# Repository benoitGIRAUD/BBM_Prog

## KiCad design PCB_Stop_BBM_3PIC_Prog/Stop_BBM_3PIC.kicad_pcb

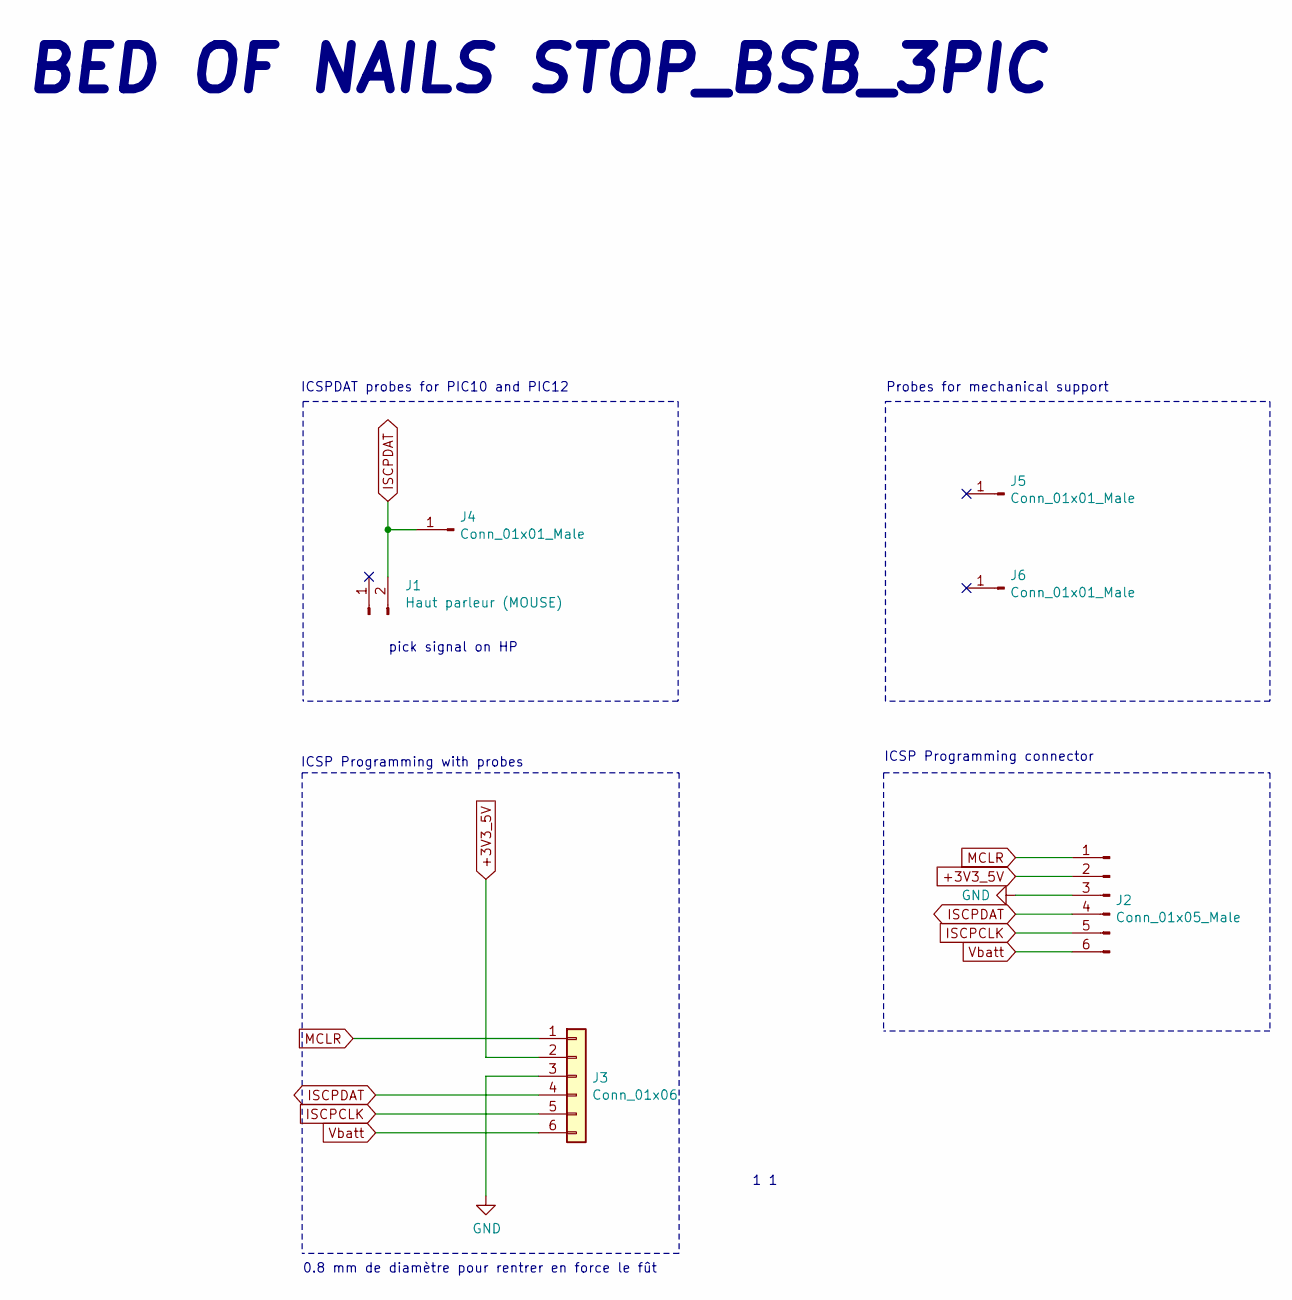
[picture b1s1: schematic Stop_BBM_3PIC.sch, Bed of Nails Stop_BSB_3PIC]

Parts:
J1: Haut parleur (MOUSE); SolderWirePad_1x01_SMD_5x10mm_BBM; Manufacturer PN ABS-209-RC
J2: Conn_01x05_Male; PinHeader_1x06_P2.54mm_Horizontal
J3: Conn_01x06; PinHeader_1x06_P2.54mm_Vertical
J4, J5, J6: Conn_01x01_Male; PinHeader_1x01_P2.54mm_Vertical

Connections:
+3V3_5V: J2.2, J3.2
GND: J2.3, J3.3
ISCPCLK: J2.5, J3.5
ISCPDAT: J1.2, J2.4, J3.4, J4.1
MCLR: J2.1, J3.1
Vbatt: J2.6, J3.6

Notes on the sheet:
1 1
ICSP Programming with probes
BED OF NAILS STOP_BSB_3PIC
ICSP Programming connector
ICSPDAT probes for PIC10 and PIC12
Probes for mechanical support
pick signal on HP
0.8 mm de diamètre pour rentrer en force le fût

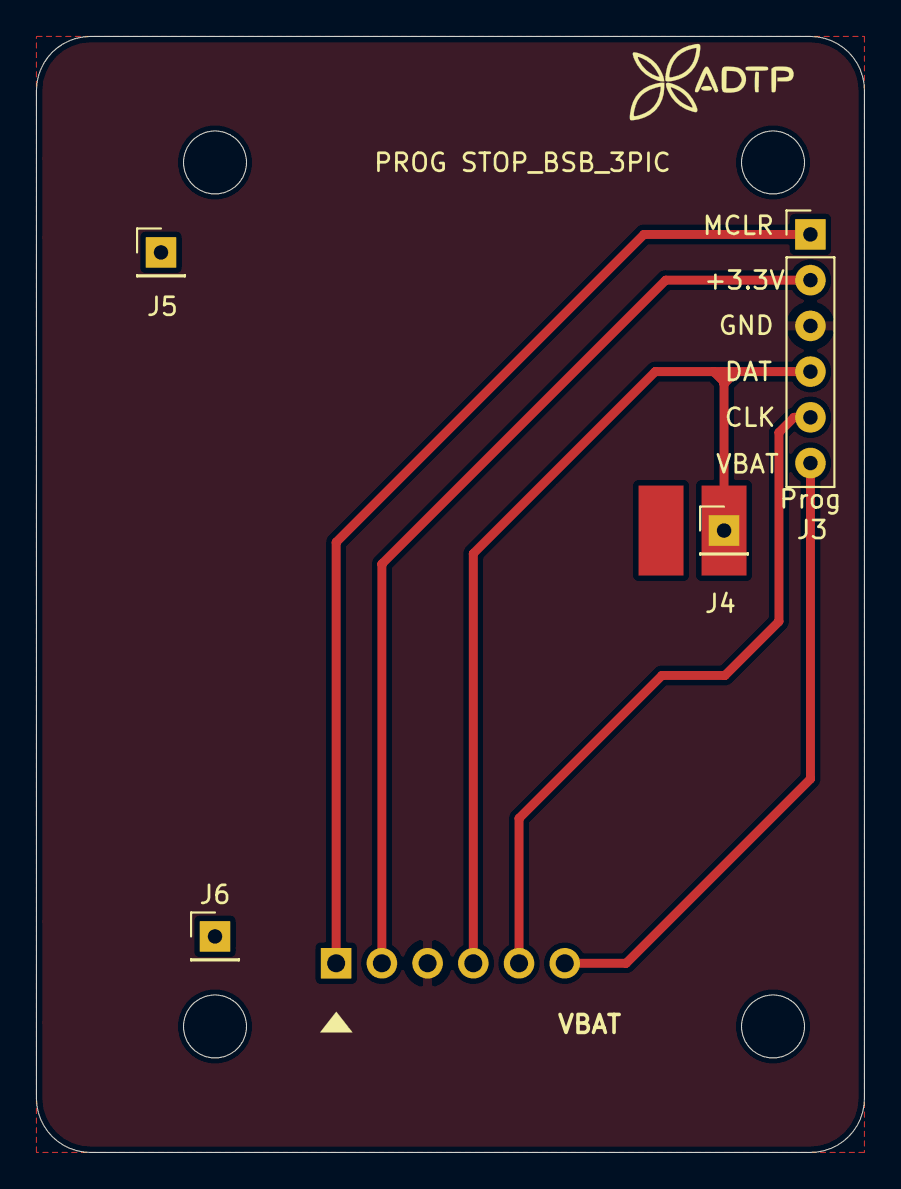
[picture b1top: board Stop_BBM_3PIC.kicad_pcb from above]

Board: 2 copper layers, 46.0 x 62.0 mm, 11 parts (1 on the bottom side), 6 nets.

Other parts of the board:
G21: LOGO; adtp
H1, H2, H3, H4: MountingHole_3.5mm

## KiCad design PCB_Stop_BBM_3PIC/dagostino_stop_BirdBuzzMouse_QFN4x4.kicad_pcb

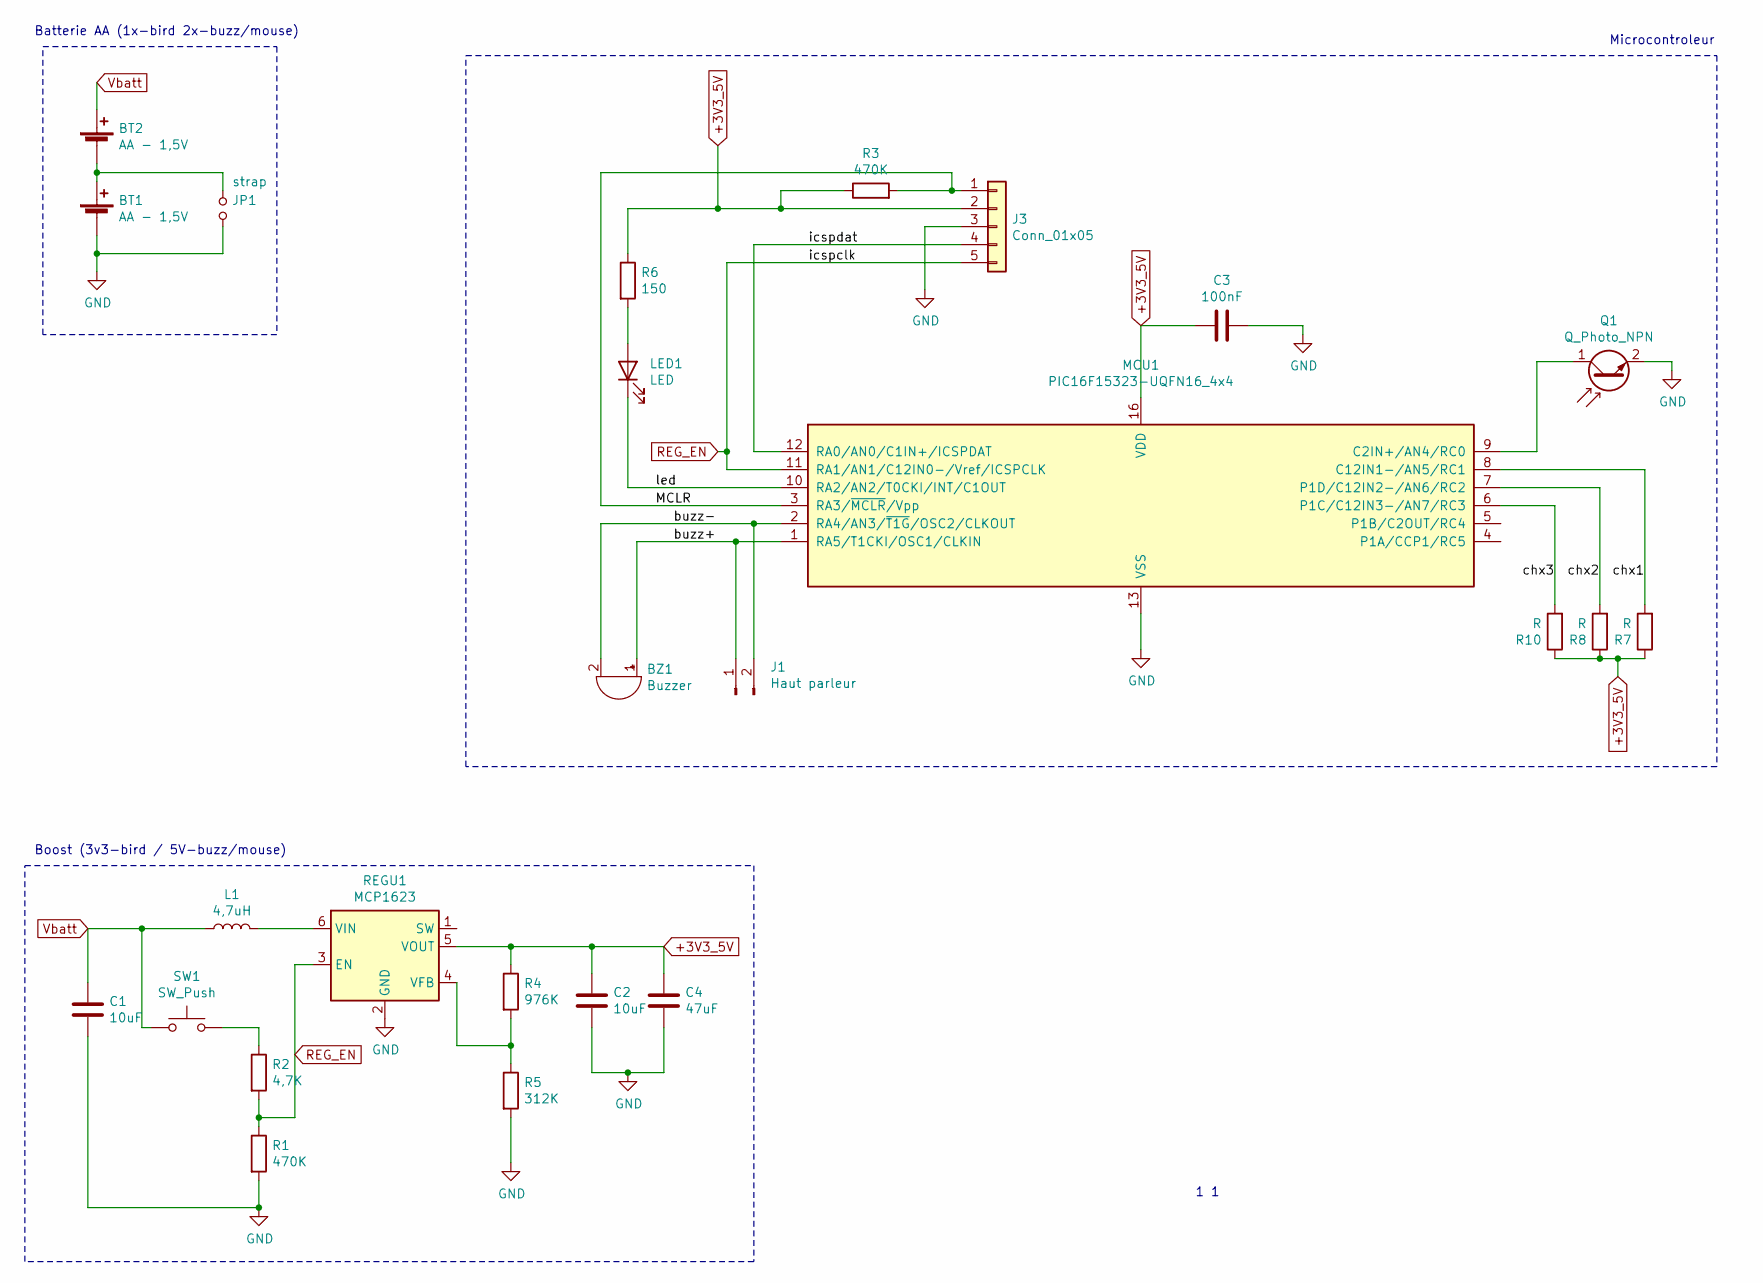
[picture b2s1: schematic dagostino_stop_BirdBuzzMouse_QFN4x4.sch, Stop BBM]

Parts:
BT1, BT2: AA - 1,5V; BatteryHolder_Keystone_2460_1xAA
BZ1: Buzzer; Buzzer_TDK_PS1240P02BT_D12.2mm_H6.5mm
C1: 10uF; C_0805_2012Metric_Pad1.18x1.45mm_HandSolder
C2: 10uF; C_0603_1608Metric_Pad1.08x0.95mm_HandSolder
C3: 100nF; C_0805_2012Metric_Pad1.18x1.45mm_HandSolder
C4: 47uF; C_1206_3216Metric_Pad1.33x1.80mm_HandSolder
J1: Haut parleur; PinHeader_1x02_P2.54mm_Vertical
J3: Conn_01x05; PinHeader_1x05_P2.54mm_Vertical
JP1: strap; SolderJumper-2_P1.3mm_Open_TrianglePad1.0x1.5mm
L1: 4,7uH; C_1210_3225Metric
LED1: LED; LED_0603_1608Metric
MCU1: PIC16F15323-UQFN16_4x4; QFN-16-1EP_4x4mm_P0.65mm_EP2.1x2.1mm; digikey PIC16F15323T-I/JQDKR-ND
Q1: Q_Photo_NPN; LED_1206_3216Metric_Pad1.42x1.75mm_HandSolder
R1, R3: 470K; R_0603_1608Metric_Pad0.98x0.95mm_HandSolder
R2: 4,7K; R_0603_1608Metric_Pad0.98x0.95mm_HandSolder
R4: 976K; R_0603_1608Metric_Pad0.98x0.95mm_HandSolder
R5: 312K; R_0603_1608Metric_Pad0.98x0.95mm_HandSolder
R6: 150; R_0603_1608Metric_Pad0.98x0.95mm_HandSolder
R7, R8, R10: R; SolderJumper-2_P1.3mm_Open_TrianglePad1.0x1.5mm
REGU1: MCP1623; SOT-23-6
SW1: SW_Push; SW_Push_1P1T_NO_6x6mm_H9.5mm

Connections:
+3V3_5V: C2.1, C3.1, C4.1, J3.2, MCU1.16 (VDD), R3.1, R4.1, R6.1, R7.1, R8.1, R10.1, REGU1.5 (VOUT)
/MCLR: J3.1, MCU1.3 (RA3/~MCLR~/Vpp), R3.2
/buzz+: BZ1.1 (-), J1.1, MCU1.1 (RA5/T1CKI/OSC1/CLKIN)
/buzz-: BZ1.2 (+), J1.2, MCU1.2 (RA4/AN3/~T1G~/OSC2/CLKOUT)
/chx1: MCU1.8 (C12IN1-/AN5/RC1), R7.2
/chx2: MCU1.7 (P1D/C12IN2-/AN6/RC2), R8.2
/chx3: MCU1.6 (P1C/C12IN3-/AN7/RC3), R10.2
/icspdat: J3.4, MCU1.12 (RA0/AN0/C1IN+/ICSPDAT)
/led: LED1.1 (K), MCU1.10 (RA2/AN2/T0CKI/INT/C1OUT)
GND: BT1.2 (-), C1.2, C2.2, C3.2, C4.2, J3.3, JP1.2, MCU1.13 (VSS), Q1.2 (E), R1.2, R5.2, REGU1.2 (GND)
unnamed: BT1.1 (+), BT2.2 (-), JP1.1
unnamed: L1.2, REGU1.6 (VIN)
unnamed: LED1.2 (A), R6.2
unnamed: MCU1.9 (C2IN+/AN4/RC0), Q1.1 (C)
unnamed: R2.1, SW1.2
unnamed: R4.2, R5.1, REGU1.4 (VFB)
REG_EN: J3.5, MCU1.11 (RA1/AN1/C12IN0-/Vref/ICSPCLK), R1.1, R2.2, REGU1.3 (EN)
Vbatt: BT2.1 (+), C1.1, L1.1, SW1.1

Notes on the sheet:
Batterie AA (1x-bird 2x-buzz/mouse)
Microcontroleur
Boost (3v3-bird / 5V-buzz/mouse)
1 1

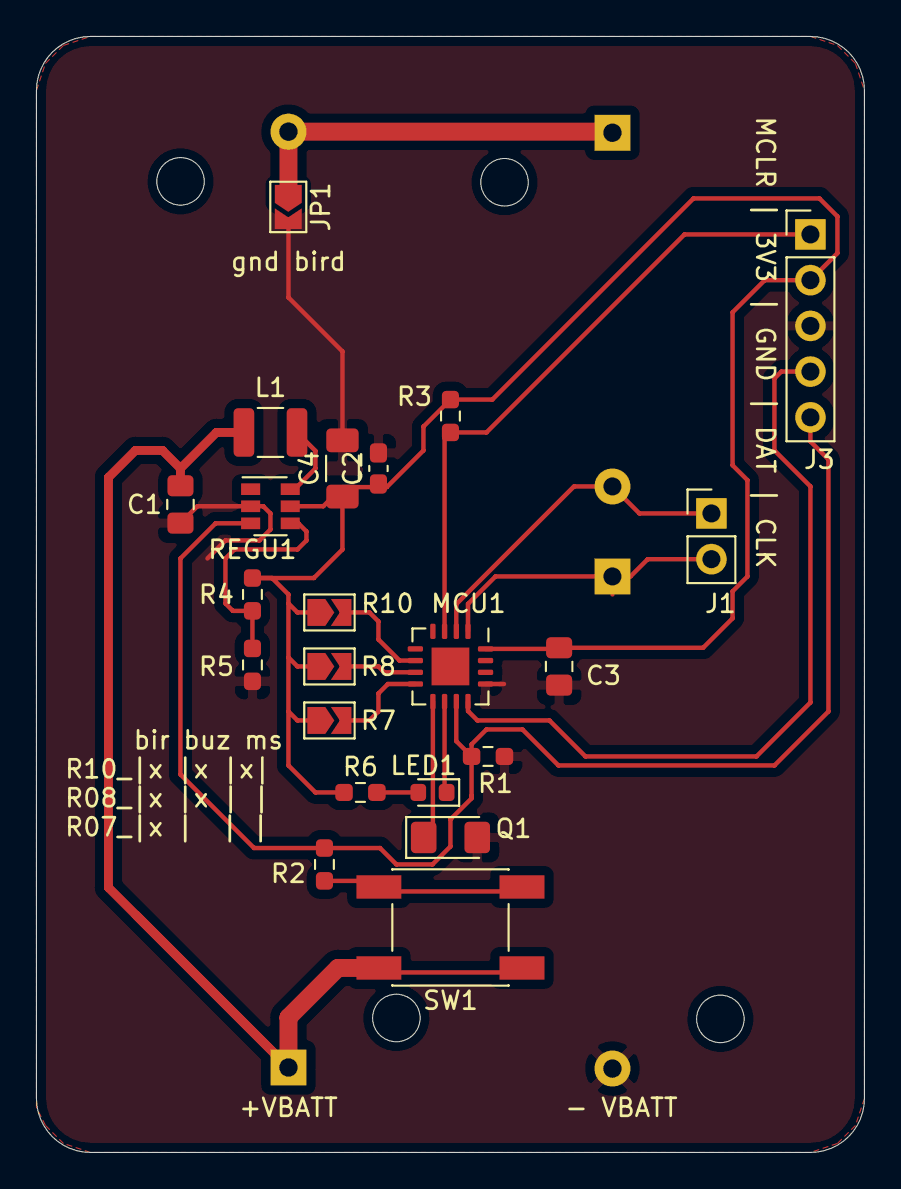
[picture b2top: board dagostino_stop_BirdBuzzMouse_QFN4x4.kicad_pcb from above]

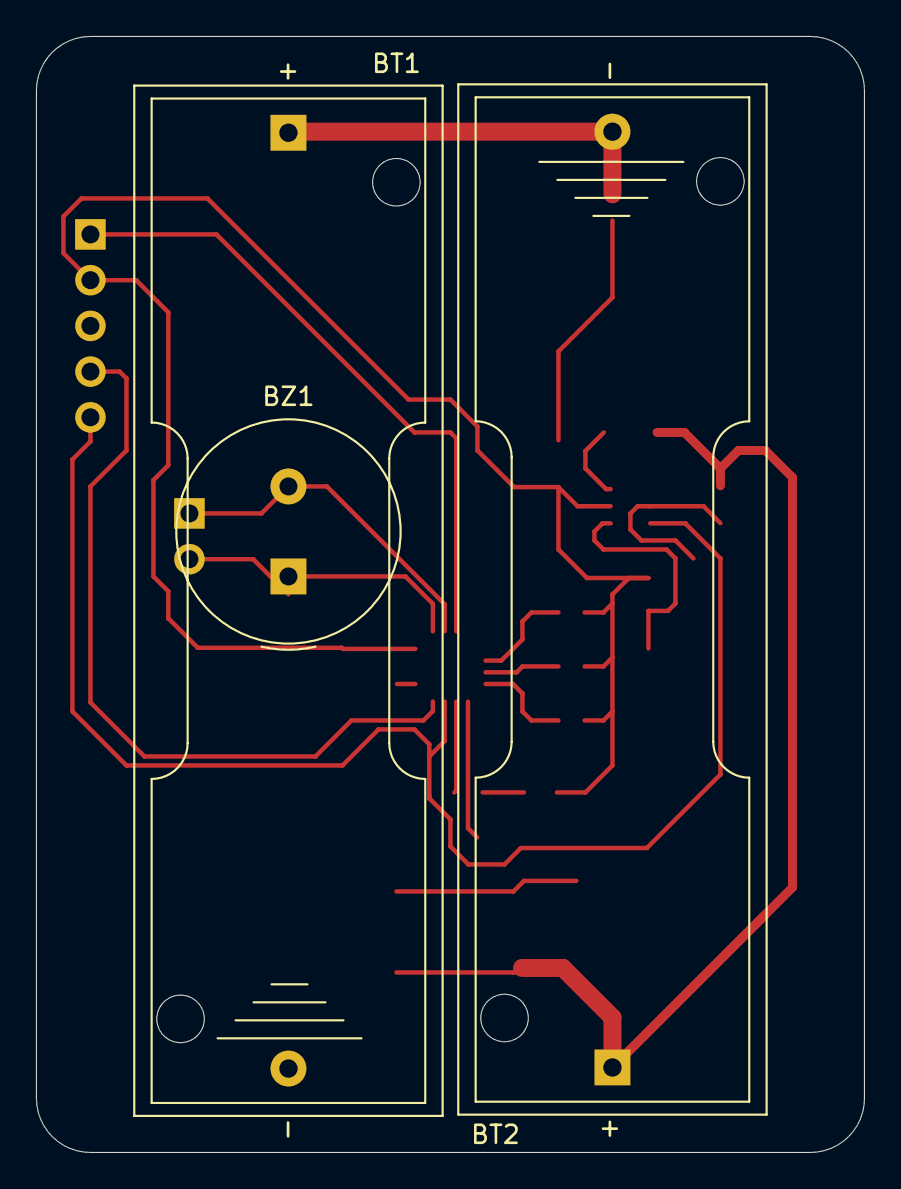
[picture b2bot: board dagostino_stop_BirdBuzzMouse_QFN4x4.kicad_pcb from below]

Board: 2 copper layers, 46.0 x 62.0 mm, 25 parts (3 on the bottom side), 18 nets.

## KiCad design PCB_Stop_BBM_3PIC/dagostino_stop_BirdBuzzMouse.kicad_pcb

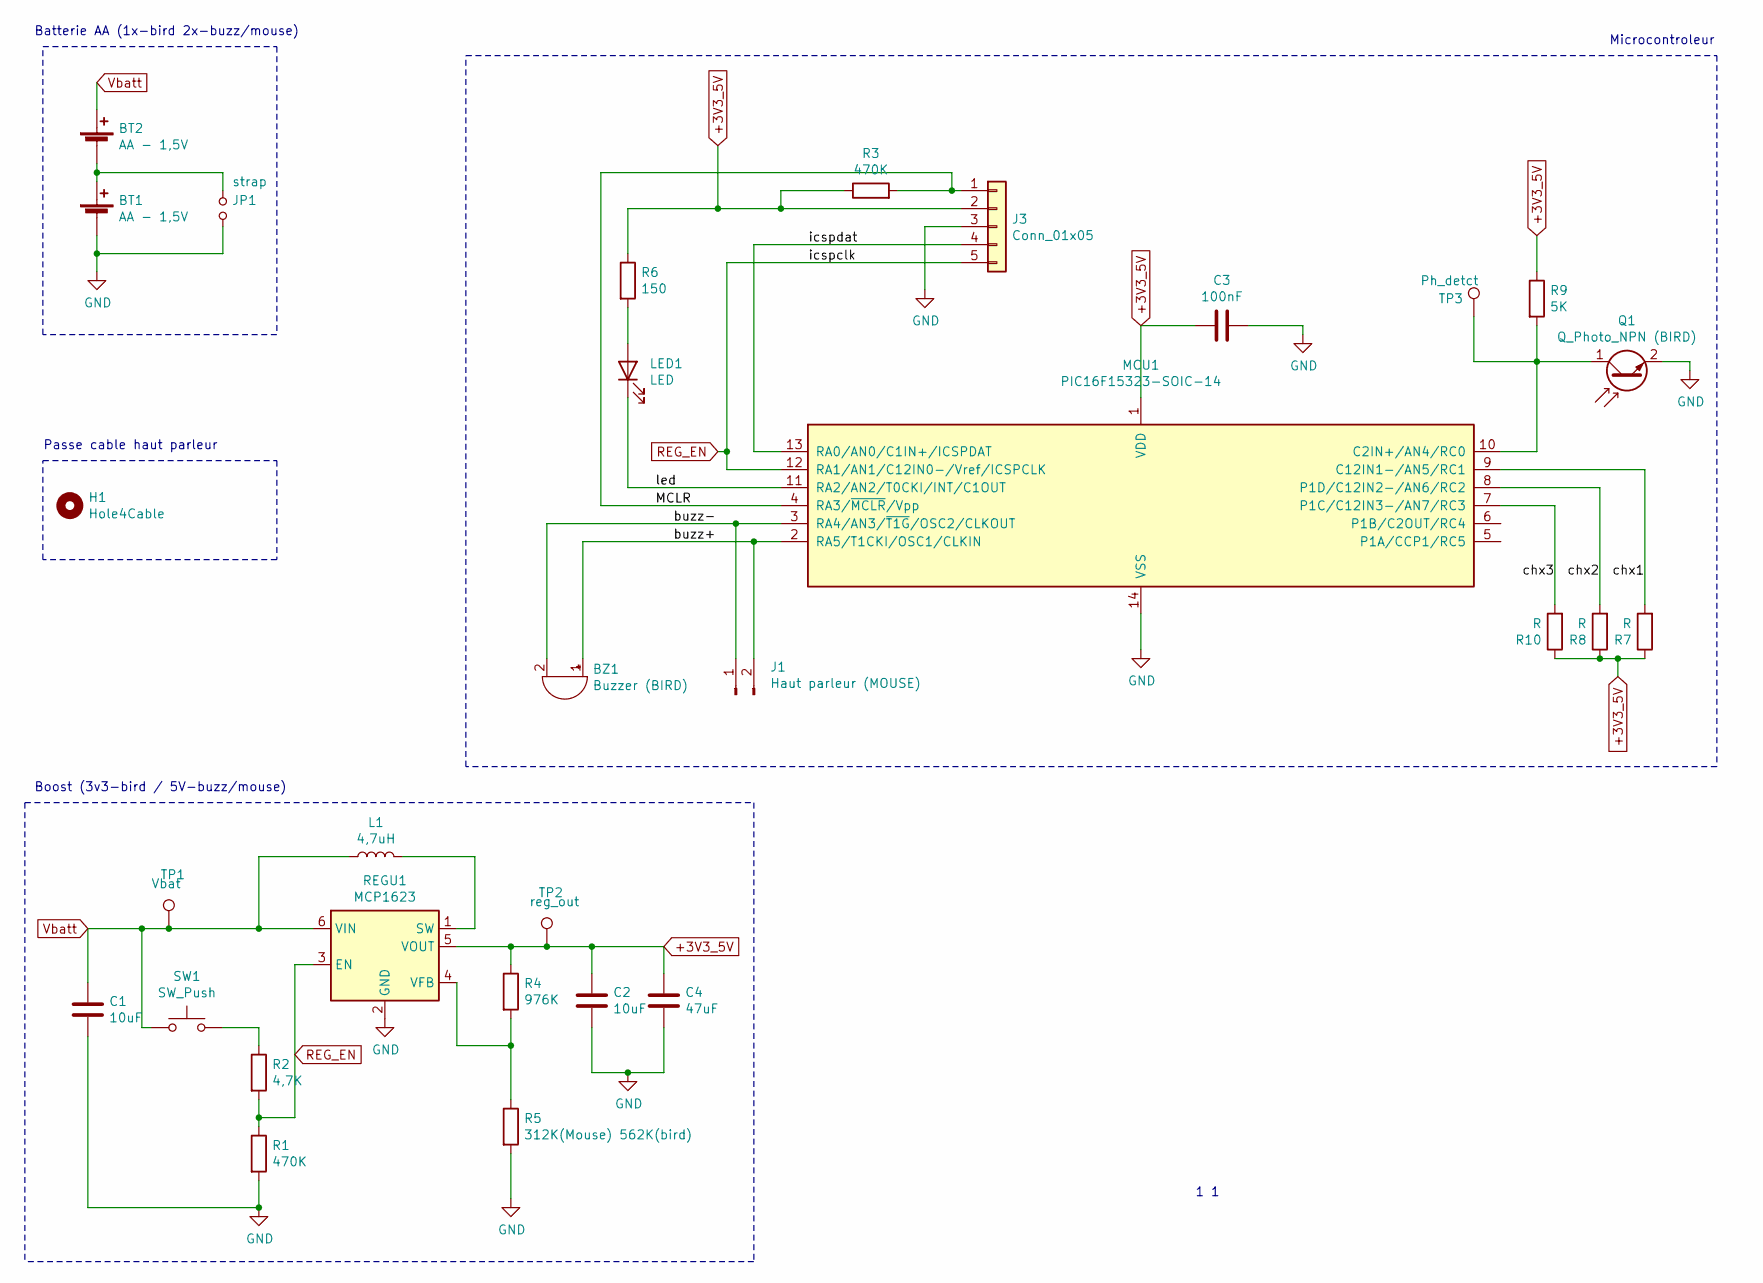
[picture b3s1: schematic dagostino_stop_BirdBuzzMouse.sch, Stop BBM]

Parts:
BT1, BT2: AA - 1,5V; BatteryHolder_Keystone_2460_1xAA; mouser 534-2460
BZ1: Buzzer (BIRD); Buzzer_TDK_PS1240P02BT_D12.2mm_H6.5mm
C1: 10uF; C_0805_2012Metric_Pad1.18x1.45mm_HandSolder
C2: 10uF; C_0603_1608Metric_Pad1.08x0.95mm_HandSolder
C3: 100nF; C_0805_2012Metric_Pad1.18x1.45mm_HandSolder
C4: 47uF; C_1206_3216Metric_Pad1.33x1.80mm_HandSolder
H1: Hole4Cable; MountingHole_3.7mm
J1: Haut parleur (MOUSE); PinHeader_1x02_P2.54mm_Vertical
J3: Conn_01x05; PinHeader_1x05_P2.54mm_Vertical
JP1: strap; SolderJumper-2_P1.3mm_Open_TrianglePad1.0x1.5mm
L1: 4,7uH; C_1210_3225Metric
LED1: LED; LED_0805_2012Metric
MCU1: PIC16F15323-SOIC-14; SOIC-14_3.9x8.7mm_P1.27mm
Q1: Q_Photo_NPN (BIRD); LED_0805_2012Metric_Pad1.15x1.40mm_HandSolder
R1, R3: 470K; R_0603_1608Metric_Pad0.98x0.95mm_HandSolder
R2: 4,7K; R_0603_1608Metric_Pad0.98x0.95mm_HandSolder
R4: 976K; R_0603_1608Metric_Pad0.98x0.95mm_HandSolder
R5: 312K(Mouse) 562K(bird); R_0603_1608Metric_Pad0.98x0.95mm_HandSolder
R6: 150; R_0603_1608Metric_Pad0.98x0.95mm_HandSolder
R7, R8, R10: R; SolderJumper-2_P1.3mm_Open_TrianglePad1.0x1.5mm
R9: 5K; R_0603_1608Metric_Pad0.98x0.95mm_HandSolder
REGU1: MCP1623; SOT-23-6; DIGIKEY MCP1623T-I/CHYTR-ND
SW1: SW_Push; SW_Push_1P1T_NO_6x6mm_H0.71mm; MOUSER 506-FSM2JSMA
TP1: Vbat; TestPoint_Pad_D2.0mm
TP2: reg_out; TestPoint_Pad_D2.0mm
TP3: Ph_detct; TestPoint_Pad_D2.0mm

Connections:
+3V3_5V: C2.1, C3.1, C4.1, J3.2, MCU1.1 (VDD), R3.1, R4.1, R6.1, R7.1, R8.1, R9.1, R10.1, REGU1.5 (VOUT), TP2.1
/MCLR: J3.1, MCU1.4 (RA3/~MCLR~/Vpp), R3.2
/buzz+: BZ1.1 (-), J1.2, MCU1.2 (RA5/T1CKI/OSC1/CLKIN)
/buzz-: BZ1.2 (+), J1.1, MCU1.3 (RA4/AN3/~T1G~/OSC2/CLKOUT)
/chx1: MCU1.9 (C12IN1-/AN5/RC1), R7.2
/chx2: MCU1.8 (P1D/C12IN2-/AN6/RC2), R8.2
/chx3: MCU1.7 (P1C/C12IN3-/AN7/RC3), R10.2
/icspdat: J3.4, MCU1.13 (RA0/AN0/C1IN+/ICSPDAT)
/led: LED1.1 (K), MCU1.11 (RA2/AN2/T0CKI/INT/C1OUT)
GND: BT1.2 (-), C1.2, C2.2, C3.2, C4.2, J3.3, JP1.2, MCU1.14 (VSS), Q1.2 (E), R1.2, R5.2, REGU1.2 (GND)
unnamed: BT1.1 (+), BT2.2 (-), JP1.1
unnamed: L1.2, REGU1.1 (SW)
unnamed: LED1.2 (A), R6.2
unnamed: MCU1.10 (C2IN+/AN4/RC0), Q1.1 (C), R9.2, TP3.1
unnamed: R2.1, SW1.2
unnamed: R4.2, R5.1, REGU1.4 (VFB)
REG_EN: J3.5, MCU1.12 (RA1/AN1/C12IN0-/Vref/ICSPCLK), R1.1, R2.2, REGU1.3 (EN)
Vbatt: BT2.1 (+), C1.1, L1.1, REGU1.6 (VIN), SW1.1, TP1.1

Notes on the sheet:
Batterie AA (1x-bird 2x-buzz/mouse)
Microcontroleur
Boost (3v3-bird / 5V-buzz/mouse)
1 1
Passe cable haut parleur

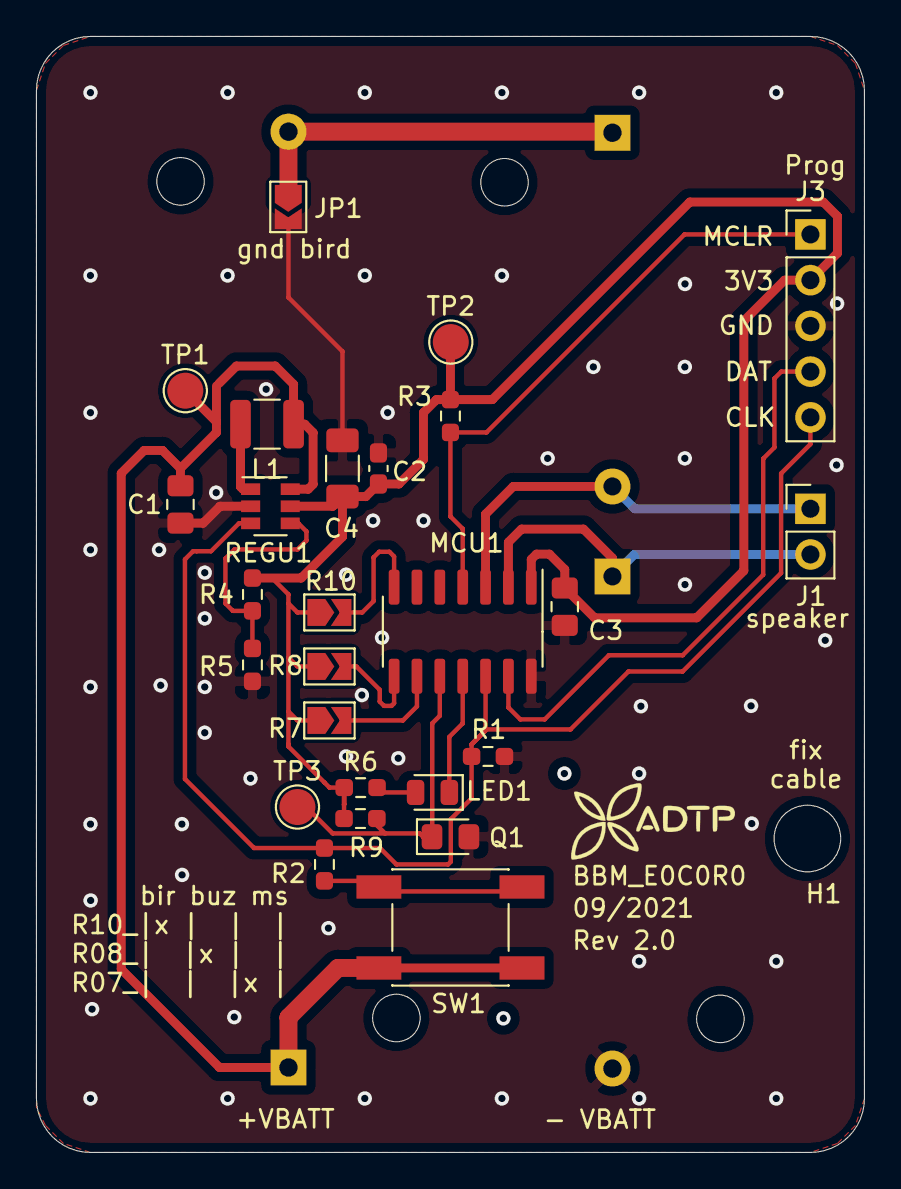
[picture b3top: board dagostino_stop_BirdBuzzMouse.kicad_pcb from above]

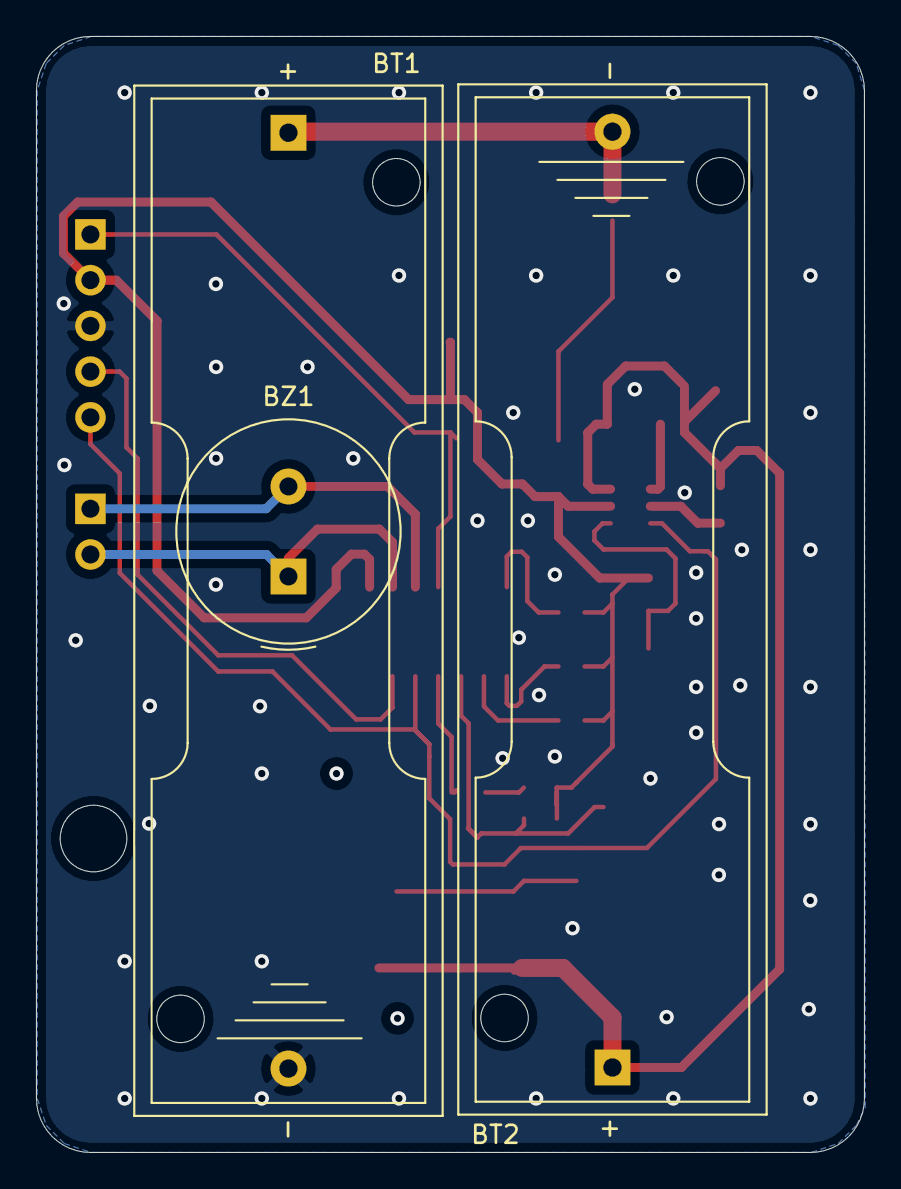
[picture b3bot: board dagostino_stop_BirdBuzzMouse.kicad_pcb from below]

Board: 2 copper layers, 46.0 x 62.0 mm, 30 parts (3 on the bottom side), 18 nets.

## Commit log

2022-06-23 PCB Finit + changement de dossier
2022-06-23 GERBER Généré
    Fabrication Menoge SUR LPKF
2022-06-23 Ajout MCLR et VBAT sur F.CU + Gerber en 3 fichiers
2022-06-26 Modifié pour EUROCIRCUIT + Devis
    discuter de la sérigraphie
2022-06-26 Cache
2022-06-29 PRODUCTION: Démo semaine prochaine
2022-06-29 production au plus court
2022-06-29 Oublie pad en 0.8 sur HP
2022-06-29 prod
